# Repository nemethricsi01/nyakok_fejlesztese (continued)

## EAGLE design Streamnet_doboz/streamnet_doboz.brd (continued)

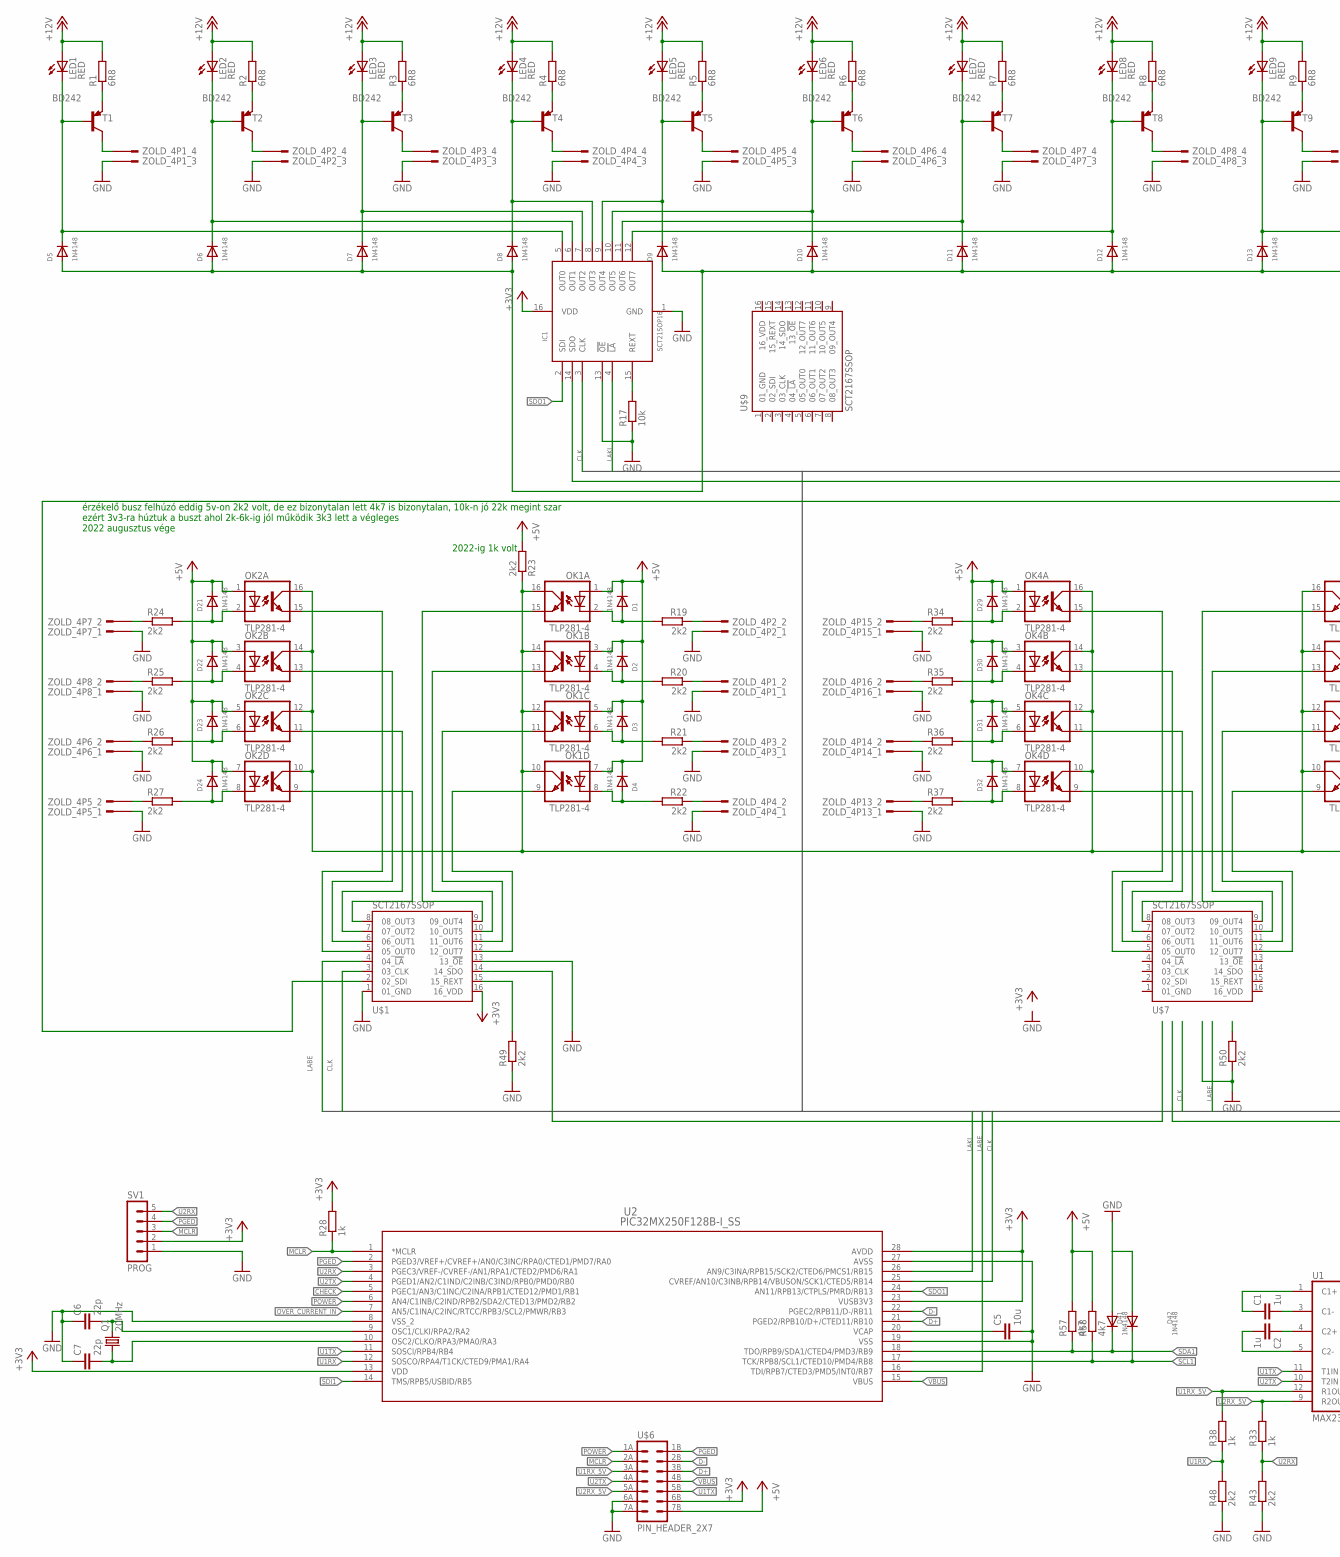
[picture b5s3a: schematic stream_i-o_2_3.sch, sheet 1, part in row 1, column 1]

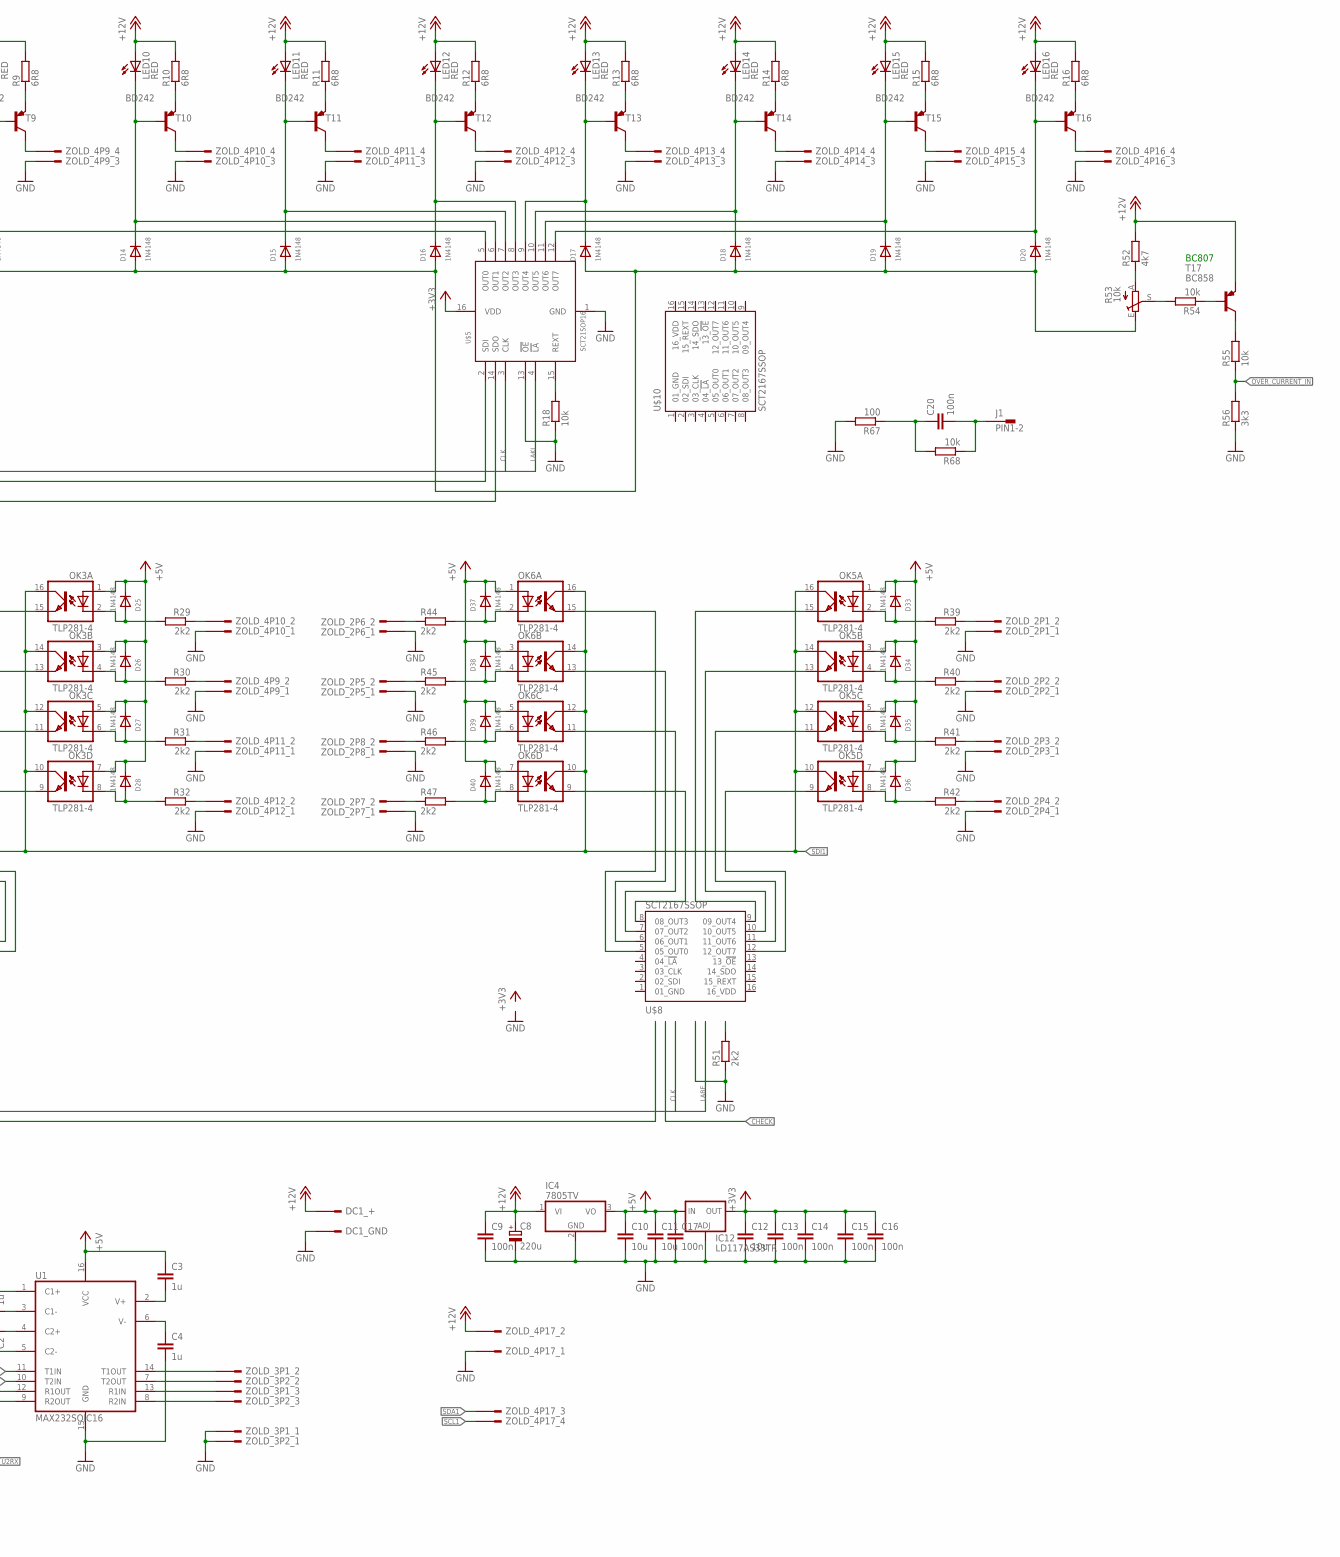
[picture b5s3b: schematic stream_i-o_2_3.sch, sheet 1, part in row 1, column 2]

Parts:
C1, C2, C3, C4: 1u; C0805
C5, C10, C11, C12: 10u; C0805
C6, C7: 22p; C0805
C8: 220u; E2,5-7
C9, C13, C14, C15, C16, C17, C20: 100n; C0805
D1, D2, D3, D4, D5, D6, D7, D8, D9, D10, D11, D12, D13, D14, D15, D16, D17, D18, D19, D20, D21, D22, D23, D24, D25, D26, D27, D28, D29, D30, D31, D32, D33, D34, D35, D36, D37, D38, D39, D40, D41, D42: 1N4148; SOD-323
DC1: DC_55/21
IC1: SCT21SOP16; SOP16
IC4: 7805TV; TO220V
IC12: LD117AS33TR; SOT223
J1: PIN1-2; 62221
LED1, LED2, LED3, LED4, LED5, LED6, LED7, LED8, LED9, LED10, LED11, LED12, LED13, LED14, LED15, LED16: RED; CHIPLED_1206
OK1, OK2, OK3, OK4, OK5, OK6: TLP281-4; MINI-FLAT-16
Q1: 20MHz; HC49UP
R1, R2, R3, R4, R5, R6, R7, R8, R9, R10, R11, R12, R13, R14, R15, R16: 6R8; R0805
R17, R18, R54, R55, R68: 10k; R0805
R19, R20, R21, R22, R23, R24, R25, R26, R27, R29, R30, R31, R32, R34, R35, R36, R37, R39, R40, R41, R42, R43, R44, R45, R46, R47, R48, R49, R50, R51: 2k2; R0805
R28, R33, R38: 1k; R0805
R52, R57, R58: 4k7; R0805
R53: 10k; PT-6
R56: 3k3; R0805
R67: 100; R0805
SV1: PROG; MA05-1
T1, T2, T3, T4, T5, T6, T7, T8, T9, T10, T11, T12, T13, T14, T15, T16: BD242; TO220V
T17: BC858; SOT23-BEC
U1: MAX232SOIC16; SO016
U2: PIC32MX250F128B-I_SS; SSOP28_MC
U$1, U$7, U$8, U$9, U$10: SCT2167SSOP; SSOP
U$5: SCT21SOP16; SOP16
U$6: PIN_HEADER_2X7
ZOLD_2P1, ZOLD_2P2, ZOLD_2P3, ZOLD_2P4, ZOLD_2P5, ZOLD_2P6, ZOLD_2P7, ZOLD_2P8: ZOLD_KICSI_2P
ZOLD_3P1, ZOLD_3P2: ZOLD_KICSI_3P
ZOLD_4P1, ZOLD_4P2, ZOLD_4P3, ZOLD_4P4, ZOLD_4P5, ZOLD_4P6, ZOLD_4P7, ZOLD_4P8, ZOLD_4P9, ZOLD_4P10, ZOLD_4P11, ZOLD_4P12, ZOLD_4P13, ZOLD_4P14, ZOLD_4P15, ZOLD_4P16, ZOLD_4P17: ZOLD_KICSI_4P

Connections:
+3V3: C12.1, C13.1, C14.1, C15.1, C16.1, IC1.16 (VDD), IC12.4 (OUT), R28.2, SV1.2, U2.13 (VDD), U2.23 (VUSB3V3), U2.28 (AVDD), U$1.16 (16_VDD), U$5.16 (VDD), U$6.6B (12); also elsewhere on the board
+5V: C3.1, C10.1, C11.1, C17.1, D1.C, D2.C, D3.C, D4.C, D21.C, D22.C, D23.C, D24.C, D25.C, D26.C, D27.C, D28.C, D29.C, D30.C, D31.C, D32.C, D33.C, D34.C, D35.C, D36.C, D37.C, D38.C, D39.C, D40.C, IC4.3 (VO), IC12.3 (IN), OK1.1 (A), OK1.3 (A), OK1.5 (A), OK1.7 (A), OK2.1 (A), OK2.3 (A), OK2.5 (A), OK2.7 (A), OK3.1 (A), OK3.3 (A), OK3.5 (A), OK3.7 (A), OK4.1 (A), OK4.3 (A), OK4.5 (A), OK4.7 (A), OK5.1 (A), OK5.3 (A), OK5.5 (A), OK5.7 (A), OK6.1 (A), OK6.3 (A), OK6.5 (A), OK6.7 (A), R23.2, R57.2, R58.2, U1.16 (VCC), U$6.7B (14); also elsewhere on the board
+12V: C8.+, C9.1, DC1.2, IC4.1 (VI), LED1.A, LED2.A, LED3.A, LED4.A, LED5.A, LED6.A, LED7.A, LED8.A, LED9.A, LED10.A, LED11.A, LED12.A, LED13.A, LED14.A, LED15.A, LED16.A, R1.2, R2.2, R3.2, R4.2, R5.2, R6.2, R7.2, R8.2, R9.2, R10.2, R11.2, R12.2, R13.2, R14.2, R15.2, R16.2, R52.2, T17.E, ZOLD_4P17.2; also elsewhere on the board
CHECK: U2.5 (PGEC1/AN3/C1INC/C2INA/RPB1/CTED12/PMD1/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); also elsewhere on the board
CLK: IC1.3 (CLK), U2.25 (CVREF/AN10/C3INB/RPB14/VBUSON/SCK1/CTED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), U$1.3 (03_CLK), U$5.3 (CLK); also elsewhere on the board
D+: U2.21 (PGED2/RPB10/D+/CTED11/RB10), U$6.3B (6)
D-: U2.22 (PGEC2/RPB11/D-/RB11), U$6.2B (4)
GND: C4.2, C5.2, C6.1, C7.1, C8.-, C9.2, C10.2, C11.2, C12.2, C13.2, C14.2, C15.2, C16.2, C17.2, D41.A, D42.A, DC1.1, IC1.1 (GND), IC1.13 (!OE), IC4.2 (GND), IC12.1 (ADJ), R17.1, R18.1, R43.1, R48.1, R49.1, R50.1, R51.1, R56.1, R67.2, SV1.1, U1.15 (GND), U2.8 (VSS_2), U2.19 (VSS), U2.27 (AVSS), U$1.1 (01_GND), U$1.13 (13_!OE!), U$5.1 (GND), U$5.13 (!OE), U$6.6A (11), U$6.7A (13), ZOLD_2P1.1, ZOLD_2P2.1, ZOLD_2P3.1, ZOLD_2P4.1, ZOLD_2P5.1, ZOLD_2P6.1, ZOLD_2P7.1, ZOLD_2P8.1, ZOLD_3P1.1, ZOLD_3P2.1, ZOLD_4P1.1, ZOLD_4P1.3, ZOLD_4P2.1, ZOLD_4P2.3, ZOLD_4P3.1, ZOLD_4P3.3, ZOLD_4P4.1, ZOLD_4P4.3, ZOLD_4P5.1, ZOLD_4P5.3, ZOLD_4P6.1, ZOLD_4P6.3, ZOLD_4P7.1, ZOLD_4P7.3, ZOLD_4P8.1, ZOLD_4P8.3, ZOLD_4P9.1, ZOLD_4P9.3, ZOLD_4P10.1, ZOLD_4P10.3, ZOLD_4P11.1, ZOLD_4P11.3, ZOLD_4P12.1, ZOLD_4P12.3, ZOLD_4P13.1, ZOLD_4P13.3, ZOLD_4P14.1, ZOLD_4P14.3, ZOLD_4P15.1, ZOLD_4P15.3, ZOLD_4P16.1, ZOLD_4P16.3, ZOLD_4P17.1; also elsewhere on the board
LABE: U2.16 (TDI/RPB7/CTED3/PMD5/INT0/RB7), U$1.4 (04_!LA!); also elsewhere on the board
LAKI: IC1.4 (!LA), U2.26 (AN9/C3INA/RPB15/SCK2/CTED6/PMCS1/RB15), U$5.4 (!LA)
MCLR: R28.1, SV1.3, U2.1 (*MCLR), U$6.2A (3)
unnamed: D8.C, IC1.8 (OUT3), LED4.C, T4.1 (B)
unnamed: D5.C, IC1.5 (OUT0), LED1.C, T1.1 (B)
unnamed: R1.1, T1.3 (E)
unnamed: T1.2 (C), ZOLD_4P1.4
unnamed: D6.C, IC1.6 (OUT1), LED2.C, T2.1 (B)
unnamed: R2.1, T2.3 (E)
unnamed: T2.2 (C), ZOLD_4P2.4
unnamed: D7.C, IC1.7 (OUT2), LED3.C, T3.1 (B)
unnamed: R3.1, T3.3 (E)
unnamed: T3.2 (C), ZOLD_4P3.4
unnamed: R4.1, T4.3 (E)
unnamed: T4.2 (C), ZOLD_4P4.4
unnamed: D9.C, IC1.9 (OUT4), LED5.C, T5.1 (B)
unnamed: R5.1, T5.3 (E)
unnamed: T5.2 (C), ZOLD_4P5.4
unnamed: D10.C, IC1.10 (OUT5), LED6.C, T6.1 (B)
unnamed: R6.1, T6.3 (E)
unnamed: T6.2 (C), ZOLD_4P6.4
unnamed: D11.C, IC1.11 (OUT6), LED7.C, T7.1 (B)
unnamed: R7.1, T7.3 (E)
unnamed: T7.2 (C), ZOLD_4P7.4
unnamed: D12.C, IC1.12 (OUT7), LED8.C, T8.1 (B)
unnamed: R8.1, T8.3 (E)
unnamed: T8.2 (C), ZOLD_4P8.4
unnamed: IC1.15 (REXT), R17.2
unnamed: R18.2, U$5.15 (REXT)
unnamed: IC1.14 (SDO), U$5.2 (SDI)
unnamed: R20.1, ZOLD_4P1.2
unnamed: D1.A, OK1.2 (C), R19.2
unnamed: R19.1, ZOLD_4P2.2
unnamed: D2.A, OK1.4 (C), R20.2
unnamed: R21.1, ZOLD_4P3.2
unnamed: D13.C, LED9.C, T9.1 (B), U$5.5 (OUT0)
unnamed: R9.1, T9.3 (E)
unnamed: T9.2 (C), ZOLD_4P9.4
unnamed: D14.C, LED10.C, T10.1 (B), U$5.6 (OUT1)
unnamed: R10.1, T10.3 (E)
unnamed: T10.2 (C), ZOLD_4P10.4
unnamed: D15.C, LED11.C, T11.1 (B), U$5.7 (OUT2)
unnamed: R11.1, T11.3 (E)
unnamed: T11.2 (C), ZOLD_4P11.4
unnamed: D16.C, LED12.C, T12.1 (B), U$5.8 (OUT3)
unnamed: R12.1, T12.3 (E)
unnamed: T12.2 (C), ZOLD_4P12.4
unnamed: D17.C, LED13.C, T13.1 (B), U$5.9 (OUT4)
unnamed: R13.1, T13.3 (E)
unnamed: T13.2 (C), ZOLD_4P13.4
unnamed: D18.C, LED14.C, T14.1 (B), U$5.10 (OUT5)
unnamed: R14.1, T14.3 (E)
unnamed: T14.2 (C), ZOLD_4P14.4
unnamed: D19.C, LED15.C, T15.1 (B), U$5.11 (OUT6)
unnamed: R15.1, T15.3 (E)
unnamed: T15.2 (C), ZOLD_4P15.4
unnamed: D20.C, LED16.C, T16.1 (B), U$5.12 (OUT7)
unnamed: R16.1, T16.3 (E)
unnamed: T16.2 (C), ZOLD_4P16.4
unnamed: D3.A, OK1.6 (C), R21.2
unnamed: R22.1, ZOLD_4P4.2
unnamed: D4.A, OK1.8 (C), R22.2
unnamed: R35.1, ZOLD_4P16.2
unnamed: D5.A, D6.A, D7.A, D8.A, D9.A, D10.A, D11.A, D12.A, D13.A, D14.A, D15.A, D16.A, D17.A, D18.A, D19.A, D20.A, R53.E
unnamed: D25.A, OK3.2 (C), R29.2
unnamed: D26.A, OK3.4 (C), R30.2
unnamed 74: OK1.15 (EMIT), U$1.9 (09_OUT4); also elsewhere on the board
unnamed 75: OK1.13 (EMIT), U$1.10 (10_OUT5); also elsewhere on the board
unnamed 76: OK1.11 (EMIT), U$1.11 (11_OUT6); also elsewhere on the board
unnamed 77: OK1.9 (EMIT), U$1.12 (12_OUT7); also elsewhere on the board
unnamed: D21.A, OK2.2 (C), R24.2
unnamed: D22.A, OK2.4 (C), R25.2
unnamed: D23.A, OK2.6 (C), R26.2
unnamed: D24.A, OK2.8 (C), R27.2
unnamed: R25.1, ZOLD_4P8.2
unnamed: R24.1, ZOLD_4P7.2
unnamed: R26.1, ZOLD_4P6.2
unnamed: R27.1, ZOLD_4P5.2
unnamed 86: OK5.15 (EMIT), U$8.9 (09_OUT4); also elsewhere on the board
unnamed 87: OK2.15 (EMIT), U$1.5 (05_OUT0); also elsewhere on the board
unnamed 88: OK2.13 (EMIT), U$1.6 (06_OUT1); also elsewhere on the board
unnamed 89: OK2.11 (EMIT), U$1.7 (07_OUT2); also elsewhere on the board
unnamed 90: OK2.9 (EMIT), U$1.8 (08_OUT3); also elsewhere on the board
unnamed: D27.A, OK3.6 (C), R31.2
unnamed: D28.A, OK3.8 (C), R32.2
unnamed: R30.1, ZOLD_4P9.2
unnamed: R29.1, ZOLD_4P10.2
unnamed: R31.1, ZOLD_4P11.2
unnamed: R32.1, ZOLD_4P12.2
unnamed: R34.1, ZOLD_4P15.2
unnamed 98: OK3.15 (EMIT), U$7.9 (09_OUT4); also elsewhere on the board
unnamed 99: OK3.13 (EMIT), U$7.10 (10_OUT5); also elsewhere on the board
unnamed 100: OK3.11 (EMIT), U$7.11 (11_OUT6); also elsewhere on the board
unnamed 101: OK3.9 (EMIT), U$7.12 (12_OUT7); also elsewhere on the board
unnamed: D29.A, OK4.2 (C), R34.2
unnamed: D30.A, OK4.4 (C), R35.2
unnamed: D31.A, OK4.6 (C), R36.2
unnamed: D32.A, OK4.8 (C), R37.2
unnamed 106: OK5.13 (EMIT), U$8.10 (10_OUT5); also elsewhere on the board
unnamed: R36.1, ZOLD_4P14.2
unnamed: R37.1, ZOLD_4P13.2
unnamed 110: OK5.11 (EMIT), U$8.11 (11_OUT6); also elsewhere on the board
unnamed 111: OK4.15 (EMIT), U$7.5 (05_OUT0); also elsewhere on the board
unnamed 112: OK4.11 (EMIT), U$7.7 (07_OUT2); also elsewhere on the board
unnamed 113: OK4.9 (EMIT), U$7.8 (08_OUT3); also elsewhere on the board
unnamed: D33.A, OK5.2 (C), R39.2
unnamed: D34.A, OK5.4 (C), R40.2
unnamed: D35.A, OK5.6 (C), R41.2
unnamed: D36.A, OK5.8 (C), R42.2
unnamed: R39.1, ZOLD_2P1.2
unnamed: R40.1, ZOLD_2P2.2
unnamed: R41.1, ZOLD_2P3.2
unnamed: R42.1, ZOLD_2P4.2
unnamed 122: OK5.9 (EMIT), U$8.12 (12_OUT7); also elsewhere on the board
unnamed: R45.1, ZOLD_2P5.2
unnamed: R47.1, ZOLD_2P7.2
unnamed: R44.1, ZOLD_2P6.2
unnamed: R46.1, ZOLD_2P8.2
unnamed: D37.A, OK6.2 (C), R44.2
unnamed: D38.A, OK6.4 (C), R45.2
unnamed: D39.A, OK6.6 (C), R46.2
unnamed: D40.A, OK6.8 (C), R47.2
unnamed: C1.2, U1.3 (C1-)
unnamed: C1.1, U1.1 (C1+)
unnamed: C2.1, U1.4 (C2+)
unnamed: C2.2, U1.5 (C2-)
unnamed: C3.2, U1.2 (V+)
unnamed 136: OK6.15 (EMIT), U$8.5 (05_OUT0); also elsewhere on the board
unnamed 137: OK6.13 (EMIT), U$8.6 (06_OUT1); also elsewhere on the board
unnamed 138: OK6.11 (EMIT), U$8.7 (07_OUT2); also elsewhere on the board
unnamed 139: OK6.9 (EMIT), U$8.8 (08_OUT3); also elsewhere on the board
unnamed 140: R51.2; also elsewhere on the board
unnamed 141: R50.2; also elsewhere on the board
unnamed 142: R49.2, U$1.15 (15_REXT); also elsewhere on the board
unnamed 143: U$1.2 (02_SDI), U$5.14 (SDO); also elsewhere on the board
unnamed: U1.14 (T1OUT), ZOLD_3P1.2
unnamed: C4.1, U1.6 (V-)
unnamed: U1.13 (R1IN), ZOLD_3P1.3
unnamed: U1.7 (T2OUT), ZOLD_3P2.2
unnamed: U1.8 (R2IN), ZOLD_3P2.3
unnamed: C5.1, U2.20 (VCAP)
unnamed: R52.1, R53.A
unnamed: R53.S, R54.2
unnamed: R54.1, T17.B
unnamed: R55.2, T17.C
unnamed: C7.2, Q1.1, U2.10 (OSC2/CLKO/RPA3/PMA0/RA3)
unnamed: C6.2, Q1.2, U2.9 (OSC1/CLKI/RPA2/RA2)
unnamed: C20.1, R67.1, R68.2
unnamed: C20.2, J1.1, R68.1
OVER_CURRENT_IN: R55.1, R56.2, U2.7 (AN5/C1INA/C2INC/RTCC/RPB3/SCL2/PMWR/RB3)
PGED: SV1.4, U2.2 (PGED3/VREF+/CVREF+/AN0/C3INC/RPA0/CTED1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), U$6.1B (2)
POWER: U2.6 (AN4/C1INB/C2IND/RPB2/SDA2/CTED13/PMD2/R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), U$6.1A (1)
SCL1: D42.C, R58.1, U2.17 (TCK/RPB8/SCL1/CTED10/PMD4/RB8), ZOLD_4P17.4
SDA1: D41.C, R57.1, U2.18 (TDO/RPB9/SDA1/CTED4/PMD3/RB9), ZOLD_4P17.3
SDI1: OK1.10 (COL), OK1.12 (COL), OK1.14 (COL), OK1.16 (COL), OK2.10 (COL), OK2.12 (COL), OK2.14 (COL), OK2.16 (COL), OK3.10 (COL), OK3.12 (COL), OK3.14 (COL), OK3.16 (COL), OK4.10 (COL), OK4.12 (COL), OK4.14 (COL), OK4.16 (COL), OK5.10 (COL), OK5.12 (COL), OK5.14 (COL), OK5.16 (COL), OK6.10 (COL), OK6.12 (COL), OK6.14 (COL), OK6.16 (COL), R23.1, U2.14 (TMS/RPB5/USBID/RB5)
SDO1: IC1.2 (SDI), U2.24 (AN11/RPB13/CTPLS/PMRD/RB13)
U1RX: R38.1, R48.2, U2.12 (SOSCO/RPA4/T1CK/CTED9/PMA1/RA4)
U1RX_5V: R38.2, U1.12 (R1OUT), U$6.3A (5)
U1TX: U1.11 (T1IN), U2.11 (SOSCI/RPB4/RB4), U$6.5B (10)
U2RX: R33.1, R43.2, SV1.5, U2.3 (PGEC3/VREF-/CVREF-/AN1/RPA1/CTED2/PMD6/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)
U2RX_5V: R33.2, U1.9 (R2OUT), U$6.5A (9)
U2TX: U1.10 (T2IN), U2.4 (PGED1/AN2/C1IND/C2INB/C3IND/RPB0/PMD0/R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), U$6.4A (7)
VBUS: U2.15 (VBUS), U$6.4B (8)

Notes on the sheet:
2022-ig 1k volt
érzékelő busz felhúzó eddig 5v-on 2k2 volt, de ez bizonytalan lett 4k7 is bizonytalan, 10k-n jó 22k megint szar ezért 3v3-ra húztuk a buszt ahol 2k-6k-ig jól működik 3k3 lett a végleges 2022 augusztus vége
BC807

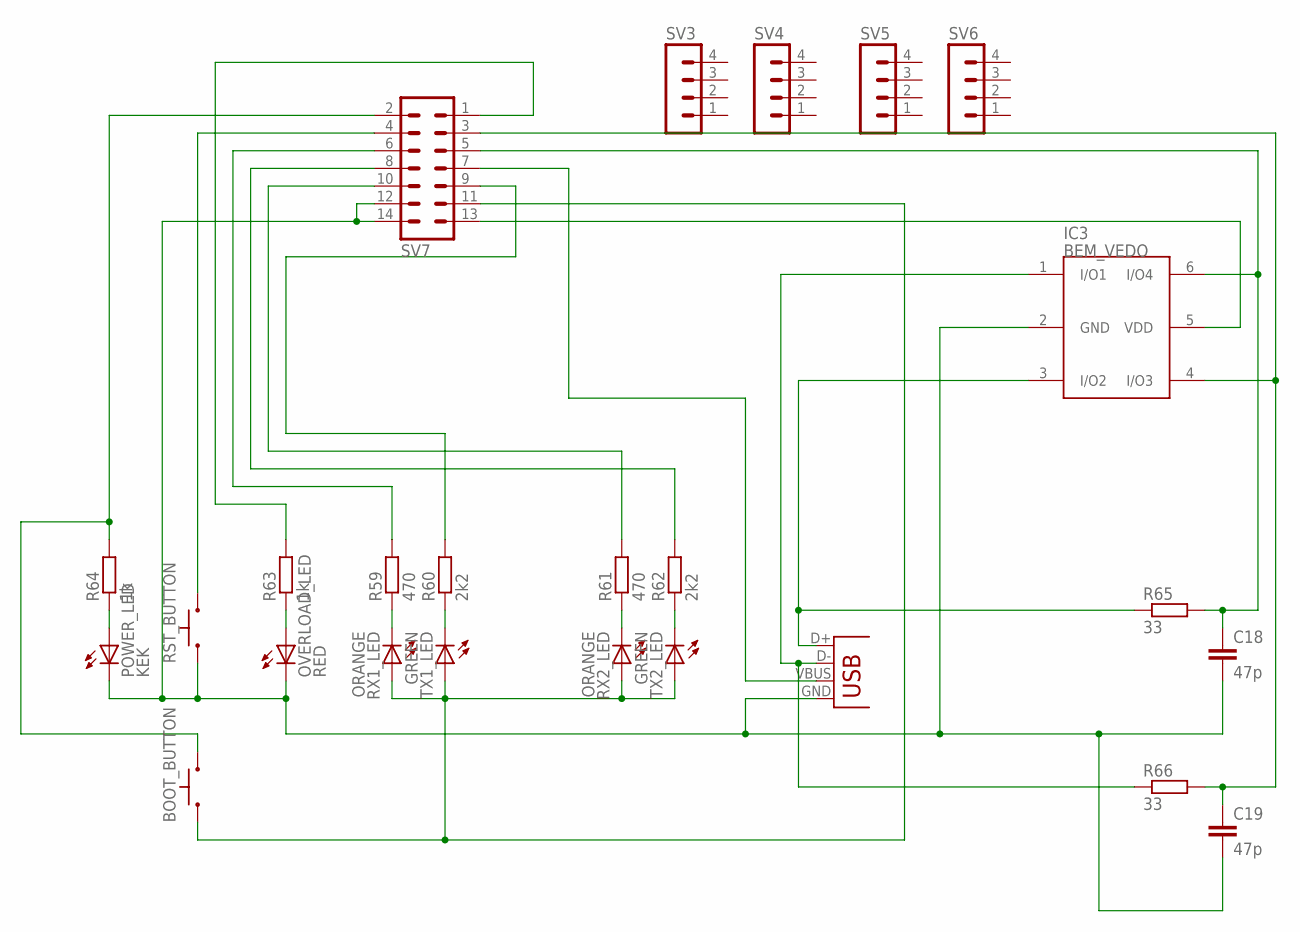
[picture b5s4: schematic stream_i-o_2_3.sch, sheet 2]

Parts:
BOOT_BUTTON: BUTTONRACON12; RACON12
C18, C19: 47p; C0805
IC3: BEM_VEDO; TSOP-6
JP1: USBPTH-VERTICAL; USB-B-PTH-VERTICAL
OVERLOAD_LED: RED; LED5MM
POWER_LED: KEK; LED5MM
R59, R61: 470; R0805
R60, R62: 2k2; R0805
R63, R64: 1k; R0805
R65, R66: 33; R0805
RST_BUTTON: BUTTONRACON12; RACON12
RX1_LED, RX2_LED: ORANGE; LED5MM
SV3, SV4, SV5, SV6: MA04-1
SV7: MA07-2
TX1_LED, TX2_LED: GREEN; LED5MM

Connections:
unnamed 163: IC3.5 (VDD), SV7.13; also elsewhere on the board
unnamed 164: RST_BUTTON.3 (S), RST_BUTTON.4 (S), SV7.4; also elsewhere on the board
unnamed 165: R59.2, SV7.6; also elsewhere on the board
unnamed 166: R60.2, SV7.9; also elsewhere on the board
unnamed 167: R61.2, SV7.10; also elsewhere on the board
unnamed 168: R62.2, SV7.8; also elsewhere on the board
unnamed: POWER_LED.A, R64.1
unnamed: OVERLOAD_LED.A, R63.1
unnamed: IC3.3 (I/O2), JP1.D+, R65.1
unnamed 172: BOOT_BUTTON.3 (S), BOOT_BUTTON.4 (S), R64.2, SV7.2; also elsewhere on the board
unnamed 173: R63.2, SV7.1; also elsewhere on the board
unnamed 174: C18.1, IC3.6 (I/O4), R65.2, SV7.5; also elsewhere on the board
unnamed 175: JP1.VBUS, SV7.7; also elsewhere on the board
unnamed 176: C19.1, IC3.4 (I/O3), R66.2, SV7.3; also elsewhere on the board
unnamed: IC3.1 (I/O1), JP1.D-, R66.1

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
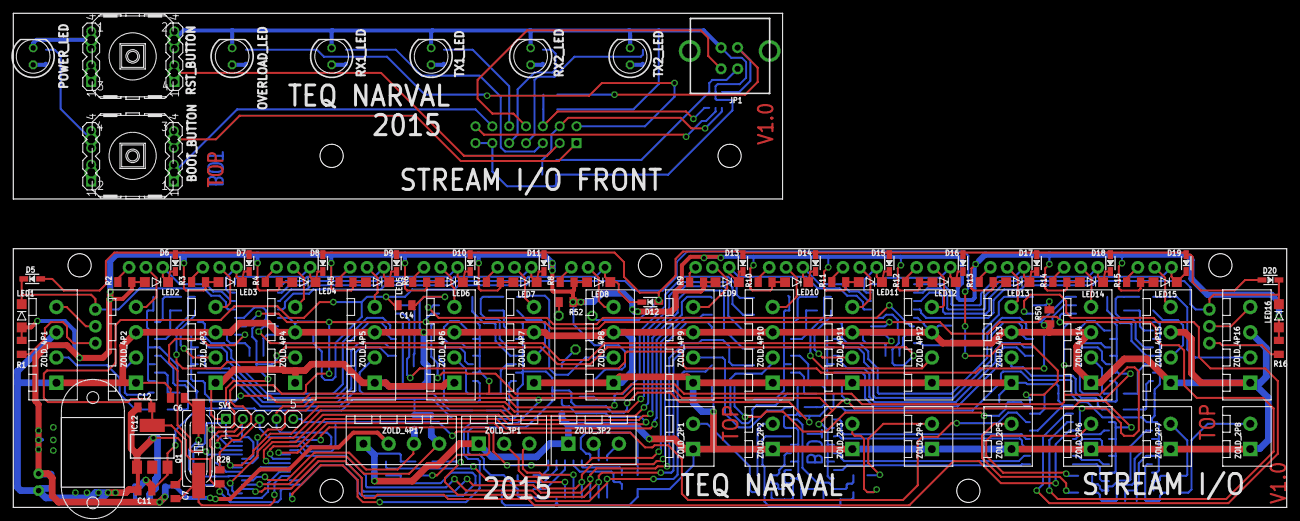
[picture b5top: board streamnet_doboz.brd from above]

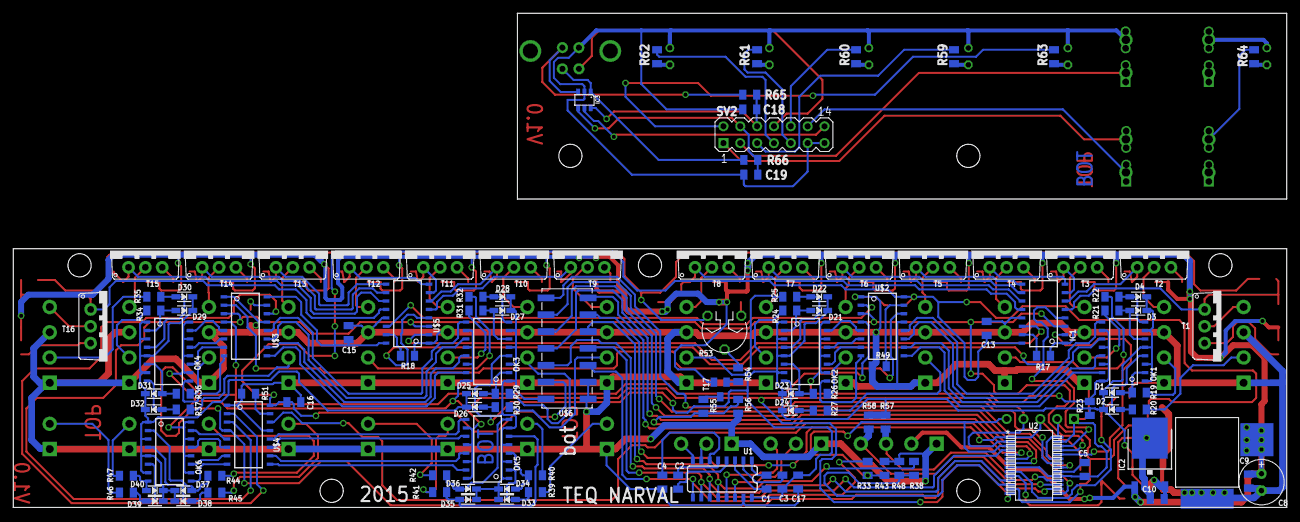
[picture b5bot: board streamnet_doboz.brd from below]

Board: 2 copper layers, 192.0 x 39.0 mm, 219 parts (119 on the bottom side), 193 nets.

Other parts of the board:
IC2: 7805DT; TO252
SV2: MA07-2

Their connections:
+5V: IC2.2; also elsewhere on the board
+12V: IC2.1; also elsewhere on the board
GND: IC2.3; also elsewhere on the board
unnamed 163: SV2.14; also elsewhere on the board
unnamed 164: SV2.3; also elsewhere on the board
unnamed 165: SV2.5; also elsewhere on the board
unnamed 166: SV2.10; also elsewhere on the board
unnamed 167: SV2.9; also elsewhere on the board
unnamed 168: SV2.7; also elsewhere on the board
unnamed 172: SV2.1; also elsewhere on the board
unnamed 173: SV2.2; also elsewhere on the board
unnamed 174: SV2.6; also elsewhere on the board
unnamed 175: SV2.8; also elsewhere on the board
unnamed 176: SV2.4; also elsewhere on the board

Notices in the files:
parts and their libraries:
microbuilder: This work is placed in the public domain, and may be freely used for commercial and non-commercial work with the following conditions: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
SparkFun-DigitalIC: Licensing: Creative Commons ShareAlike 4.0 International - https://creativecommons.org/licenses/by-sa/4.0
